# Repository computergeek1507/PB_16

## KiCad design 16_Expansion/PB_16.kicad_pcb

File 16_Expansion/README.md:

# Copyright and Disclaimer
Copyright: Scott Hanson

This documentation describes Open Hardware and is licensed under the CERN Open Hardware License Version 2 - Strongly Reciprocal. (CERN-OHL-S)

You may redistribute and modify this documentation under the terms of the CERN OHL-S-v2 (https://ohwr.org/cern_ohl_s_v2.txt). This documentation is distributed WITHOUT ANY EXPRESS OR IMPLIED WARRANTY, INCLUDING OF MERCHANTABILITY, SATISFACTORY QUALITY AND FITNESS FOR A PARTICULAR PURPOSE. Please see the CERN OHL v2-S for applicable conditions

**Under CERN OHL-S-v2, derivative work must be publicly released as defined in subsection 3.3**

# 16 Expansion

The "16 Expansion" is a 16 port output board for the PB16.  All the design files are open source and available on github.

## [Part BOM](https://github.com/computergeek1507/PB_16/raw/master/16_Expansion/16_Expansion_BOM.ods)

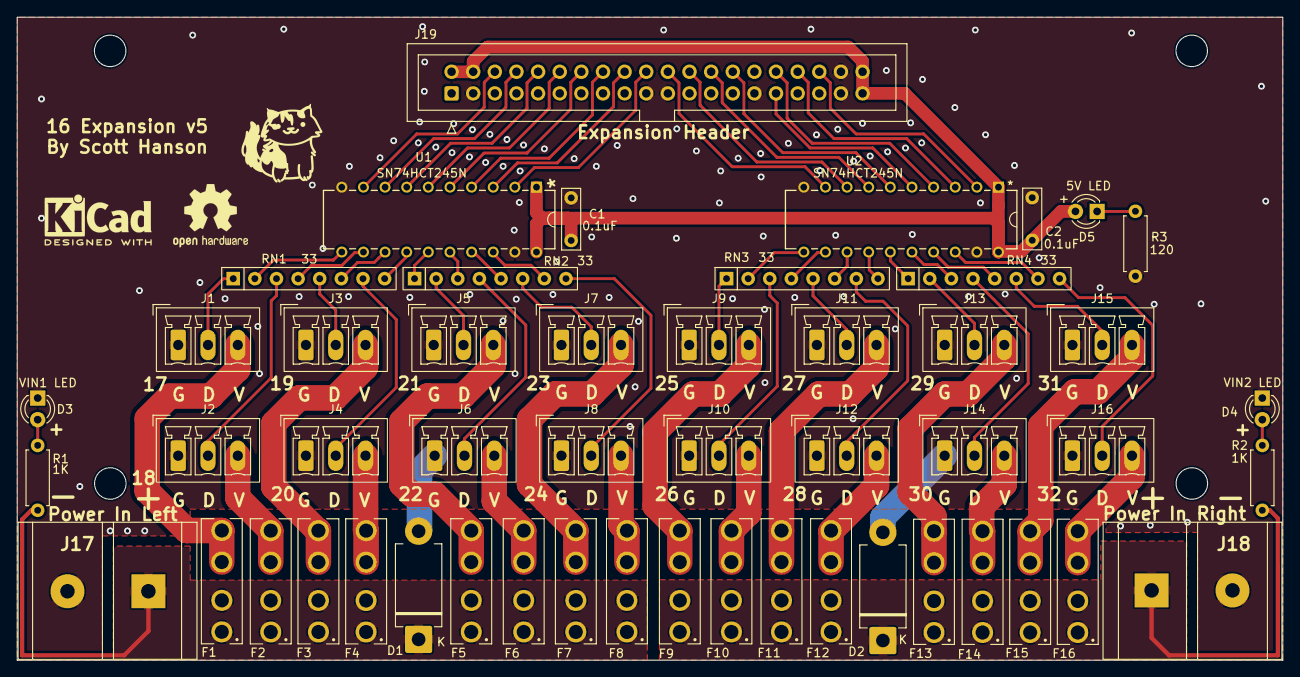
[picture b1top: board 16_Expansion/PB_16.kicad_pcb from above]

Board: 2 copper layers, 148.6 x 75.5 mm, 51 parts (0 on the bottom side), 71 nets.

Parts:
C1, C2: 0.1uF; C_Rect_L7.0mm_W2.0mm_P5.00mm
D1, D2: SB5100-T; D_DO-201AD_P12.70mm_Horizontal
D3: VIN1 LED; LED_D3.0mm
D4: VIN2 LED; LED_D3.0mm
D5: 5V LED; LED_D3.0mm
F1, F2, F3, F4, F5, F6, F7, F8, F9, F10, F11, F12, F13, F14, F15, F16: 3544-2; FUSE_3544-2
J1: String1; PhoenixContact_MCV_1,5_3-G-3.5_1x03_P3.50mm_Vertical
J2: String2; PhoenixContact_MCV_1,5_3-G-3.5_1x03_P3.50mm_Vertical
J3: String3; PhoenixContact_MCV_1,5_3-G-3.5_1x03_P3.50mm_Vertical
J4: String4; PhoenixContact_MCV_1,5_3-G-3.5_1x03_P3.50mm_Vertical
J5: String5; PhoenixContact_MCV_1,5_3-G-3.5_1x03_P3.50mm_Vertical
J6: String6; PhoenixContact_MCV_1,5_3-G-3.5_1x03_P3.50mm_Vertical
J7: String7; PhoenixContact_MCV_1,5_3-G-3.5_1x03_P3.50mm_Vertical
J8: String8; PhoenixContact_MCV_1,5_3-G-3.5_1x03_P3.50mm_Vertical
J9: String9; PhoenixContact_MCV_1,5_3-G-3.5_1x03_P3.50mm_Vertical
J10: String10; PhoenixContact_MCV_1,5_3-G-3.5_1x03_P3.50mm_Vertical
J11: String11; PhoenixContact_MCV_1,5_3-G-3.5_1x03_P3.50mm_Vertical
J12: String12; PhoenixContact_MCV_1,5_3-G-3.5_1x03_P3.50mm_Vertical
J13: String13; PhoenixContact_MCV_1,5_3-G-3.5_1x03_P3.50mm_Vertical
J14: String14; PhoenixContact_MCV_1,5_3-G-3.5_1x03_P3.50mm_Vertical
J15: String15; PhoenixContact_MCV_1,5_3-G-3.5_1x03_P3.50mm_Vertical
J16: String16; PhoenixContact_MCV_1,5_3-G-3.5_1x03_P3.50mm_Vertical
J17: Power In Left; BARRIER_BLOCK_1ROW_2POS_P9.5MM
J18: Power In Right; BARRIER_BLOCK_1ROW_2POS_P9.5MM
J19: Expansion Header; IDC-Header_2x20_P2.54mm_Vertical
R1, R2: 1K; R_Axial_DIN0207_L6.3mm_D2.5mm_P7.62mm_Horizontal
R3: 120; R_Axial_DIN0207_L6.3mm_D2.5mm_P7.62mm_Horizontal
RN1, RN2, RN3, RN4: 33; R_Array_SIP8
U1, U2: SN74HCT245N

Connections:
+5V: C1.1, C2.1, D5.2 (A), J19.2, J19.4, J19.39, J19.40, U1.1 (DIR), U1.20 (VCC), U2.1 (DIR), U2.20 (VCC)
/Output 1-8/DOUT1: J1.2, RN1.1 (R1.1)
/Output 1-8/DOUT2: J2.2, RN1.3 (R2.1)
/Output 1-8/DOUT3: J3.2, RN1.5 (R3.1)
/Output 1-8/DOUT4: J4.2, RN1.7 (R4.1)
/Output 1-8/DOUT5: J5.2, RN2.2 (R1.2)
/Output 1-8/DOUT6: J6.2, RN2.4 (R2.2)
/Output 1-8/DOUT7: J7.2, RN2.6 (R3.2)
/Output 1-8/DOUT8: J8.2, RN2.8 (R4.2)
/Output 1-8/VOUT1: F1.2_1 (2), F1.2_2 (2), J1.3
/Output 1-8/VOUT2: F2.2_1 (2), F2.2_2 (2), J2.3
/Output 1-8/VOUT3: F3.2_1 (2), F3.2_2 (2), J3.3
/Output 1-8/VOUT4: F4.2_1 (2), F4.2_2 (2), J4.3
/Output 1-8/VOUT5: F5.2_1 (2), F5.2_2 (2), J5.3
/Output 1-8/VOUT6: F6.2_1 (2), F6.2_2 (2), J6.3
/Output 1-8/VOUT7: F7.2_1 (2), F7.2_2 (2), J7.3
/Output 1-8/VOUT8: F8.2_1 (2), F8.2_2 (2), J8.3
/Output 9-16/DOUT9: J9.2, RN3.1 (R1.1)
/Output 9-16/DOUT10: J10.2, RN3.3 (R2.1)
/Output 9-16/DOUT11: J11.2, RN3.5 (R3.1)
/Output 9-16/DOUT12: J12.2, RN3.7 (R4.1)
/Output 9-16/DOUT13: J13.2, RN4.2 (R1.2)
/Output 9-16/DOUT14: J14.2, RN4.4 (R2.2)
/Output 9-16/DOUT15: J15.2, RN4.6 (R3.2)
/Output 9-16/DOUT16: J16.2, RN4.8 (R4.2)
/Output 9-16/VOUT9: F9.2_1 (2), F9.2_2 (2), J9.3
/Output 9-16/VOUT10: F10.2_1 (2), F10.2_2 (2), J10.3
/Output 9-16/VOUT11: F11.2_1 (2), F11.2_2 (2), J11.3
/Output 9-16/VOUT12: F12.2_1 (2), F12.2_2 (2), J12.3
/Output 9-16/VOUT13: F13.2_1 (2), F13.2_2 (2), J13.3
/Output 9-16/VOUT14: F14.2_1 (2), F14.2_2 (2), J14.3
/Output 9-16/VOUT15: F15.2_1 (2), F15.2_2 (2), J15.3
/Output 9-16/VOUT16: F16.2_1 (2), F16.2_2 (2), J16.3
GND: C1.2, C2.2, D1.2 (A), D2.2 (A), D3.1 (K), D4.1 (K), J1.1, J2.1, J3.1, J4.1, J5.1, J6.1, J7.1, J8.1, J9.1, J10.1, J11.1, J12.1, J13.1, J14.1, J15.1, J16.1, J17.2, J18.2, J19.3, J19.5, J19.7, J19.9, J19.11, J19.13, J19.15, J19.17, J19.19, J19.21, J19.23, J19.25, J19.27, J19.29, J19.33, J19.35, J19.37, J19.38, R3.1, U1.10 (GND), U1.19 (*OE), U2.10 (GND), U2.19 (*OE)
unnamed: D3.2 (A), R1.1
unnamed: D4.2 (A), R2.1
unnamed: D5.1 (K), R3.2
unnamed: RN1.2 (R1.2), U1.11 (B8)
unnamed: RN1.4 (R2.2), U1.12 (B7)
unnamed: RN1.6 (R3.2), U1.13 (B6)
unnamed: RN1.8 (R4.2), U1.14 (B5)
unnamed: RN2.1 (R1.1), U1.15 (B4)
unnamed: RN2.3 (R2.1), U1.16 (B3)
unnamed: RN2.5 (R3.1), U1.17 (B2)
unnamed: RN2.7 (R4.1), U1.18 (B1)
unnamed: RN3.2 (R1.2), U2.11 (B8)
unnamed: RN3.4 (R2.2), U2.12 (B7)
unnamed: RN3.6 (R3.2), U2.13 (B6)
unnamed: RN3.8 (R4.2), U2.14 (B5)
unnamed: RN4.1 (R1.1), U2.15 (B4)
unnamed: RN4.3 (R2.1), U2.16 (B3)
unnamed: RN4.5 (R3.1), U2.17 (B2)
unnamed: RN4.7 (R4.1), U2.18 (B1)
OUT17: J19.6, U1.9 (A8)
OUT18: J19.8, U1.8 (A7)
OUT19: J19.10, U1.7 (A6)
OUT20: J19.12, U1.6 (A5)
OUT21: J19.14, U1.5 (A4)
OUT22: J19.16, U1.4 (A3)
OUT23: J19.18, U1.3 (A2)
OUT24: J19.20, U1.2 (A1)
OUT25: J19.22, U2.9 (A8)
OUT26: J19.24, U2.8 (A7)
OUT27: J19.26, U2.7 (A6)
OUT28: J19.28, U2.6 (A5)
OUT29: J19.31, U2.5 (A4)
OUT30: J19.32, U2.4 (A3)
OUT31: J19.34, U2.3 (A2)
OUT32: J19.36, U2.2 (A1)
VIN1: D1.1 (K), F1.1_1 (1), F1.1_2 (1), F2.1_1 (1), F2.1_2 (1), F3.1_1 (1), F3.1_2 (1), F4.1_1 (1), F4.1_2 (1), F5.1_1 (1), F5.1_2 (1), F6.1_1 (1), F6.1_2 (1), F7.1_1 (1), F7.1_2 (1), F8.1_1 (1), F8.1_2 (1), J17.1, R1.2
VIN2: D2.1 (K), F9.1_1 (1), F9.1_2 (1), F10.1_1 (1), F10.1_2 (1), F11.1_1 (1), F11.1_2 (1), F12.1_1 (1), F12.1_2 (1), F13.1_1 (1), F13.1_2 (1), F14.1_1 (1), F14.1_2 (1), F15.1_1 (1), F15.1_2 (1), F16.1_1 (1), F16.1_2 (1), J18.1, R2.2

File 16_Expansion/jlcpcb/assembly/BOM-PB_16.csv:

Comment,Designator,Footprint,LCSC
0.1uF,C2,C_Rect_L7.0mm_W2.0mm_P5.00mm,
String2,J2,"PhoenixContact_MCV_1,5_3-G-3.5_1x03_P3.50mm_Vertical",
String5,J5,"PhoenixContact_MCV_1,5_3-G-3.5_1x03_P3.50mm_Vertical",
String6,J6,"PhoenixContact_MCV_1,5_3-G-3.5_1x03_P3.50mm_Vertical",
String7,J7,"PhoenixContact_MCV_1,5_3-G-3.5_1x03_P3.50mm_Vertical",
String8,J8,"PhoenixContact_MCV_1,5_3-G-3.5_1x03_P3.50mm_Vertical",
String9,J9,"PhoenixContact_MCV_1,5_3-G-3.5_1x03_P3.50mm_Vertical",
String10,J10,"PhoenixContact_MCV_1,5_3-G-3.5_1x03_P3.50mm_Vertical",
String11,J11,"PhoenixContact_MCV_1,5_3-G-3.5_1x03_P3.50mm_Vertical",
String12,J12,"PhoenixContact_MCV_1,5_3-G-3.5_1x03_P3.50mm_Vertical",
String13,J13,"PhoenixContact_MCV_1,5_3-G-3.5_1x03_P3.50mm_Vertical",
String14,J14,"PhoenixContact_MCV_1,5_3-G-3.5_1x03_P3.50mm_Vertical",
String15,J15,"PhoenixContact_MCV_1,5_3-G-3.5_1x03_P3.50mm_Vertical",
String16,J16,"PhoenixContact_MCV_1,5_3-G-3.5_1x03_P3.50mm_Vertical",
SN74HCT245N,U2,SN74HCT245N,
3544-2,F1,FUSE_3544-2,
3544-2,F7,FUSE_3544-2,
3544-2,F14,FUSE_3544-2,
SB5100-T,D2,D_DO-201AD_P12.70mm_Horizontal,
0.1uF,C1,C_Rect_L7.0mm_W2.0mm_P5.00mm,
3544-2,F2,FUSE_3544-2,
3544-2,F6,FUSE_3544-2,
3544-2,F8,FUSE_3544-2,
3544-2,F9,FUSE_3544-2,
3544-2,F10,FUSE_3544-2,
3544-2,F16,FUSE_3544-2,
3544-2,F5,FUSE_3544-2,
3544-2,F3,FUSE_3544-2,
3544-2,F13,FUSE_3544-2,
33,RN1,R_Array_SIP8,
3544-2,F11,FUSE_3544-2,
33,RN3,R_Array_SIP8,
33,RN4,R_Array_SIP8,
33,RN2,R_Array_SIP8,
3544-2,F4,FUSE_3544-2,
String1,J1,"PhoenixContact_MCV_1,5_3-G-3.5_1x03_P3.50mm_Vertical",
String3,J3,"PhoenixContact_MCV_1,5_3-G-3.5_1x03_P3.50mm_Vertical",
String4,J4,"PhoenixContact_MCV_1,5_3-G-3.5_1x03_P3.50mm_Vertical",
SB5100-T,D1,D_DO-201AD_P12.70mm_Horizontal,
3544-2,F15,FUSE_3544-2,
3544-2,F12,FUSE_3544-2,
SN74HCT245N,U1,SN74HCT245N,
VIN1 LED,D3,LED_D3.0mm_Clear,
1K,R1,R_Axial_DIN0207_L6.3mm_D2.5mm_P7.62mm_Horizontal,
5V LED,D5,LED_D3.0mm_Clear,
Expansion Header,J19,IDC-Header_2x20_P2.54mm_Vertical,
120,R3,R_Axial_DIN0207_L6.3mm_D2.5mm_P7.62mm_Horizontal,
Power In Left,J17,BARRIER_BLOCK_1ROW_2POS_P9.5MM,
Power In Right,J18,BARRIER_BLOCK_1ROW_2POS_P9.5MM,
1K,R2,R_Axial_DIN0207_L6.3mm_D2.5mm_P7.62mm_Horizontal,
VIN2 LED,D4,LED_D3.0mm_Clear,

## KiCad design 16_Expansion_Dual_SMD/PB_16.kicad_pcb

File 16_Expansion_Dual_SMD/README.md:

# Copyright and Disclaimer
Copyright: Scott Hanson

This documentation describes Open Hardware and is licensed under the CERN Open Hardware License Version 2 - Strongly Reciprocal. (CERN-OHL-S)

You may redistribute and modify this documentation under the terms of the CERN OHL-S-v2 (https://ohwr.org/cern_ohl_s_v2.txt). This documentation is distributed WITHOUT ANY EXPRESS OR IMPLIED WARRANTY, INCLUDING OF MERCHANTABILITY, SATISFACTORY QUALITY AND FITNESS FOR A PARTICULAR PURPOSE. Please see the CERN OHL v2-S for applicable conditions

**Under CERN OHL-S-v2, derivative work must be publicly released as defined in subsection 3.3**

# 16 Expansion Dual SMD

The "16 Expansion Dual SMD" is a 16 port output board for the PB16/BBB16. All the design files are open source and available on github.

To order PCBs upload the "GERBER-PB_16.zip" file in the "jlcpcb\gerber" folder to jlcpcb.com. Enable the SMD service, 'BOM-PB_16.csv' is the SMD BOM and 'POS-PB_16.csv' is the SMD CPL position file.

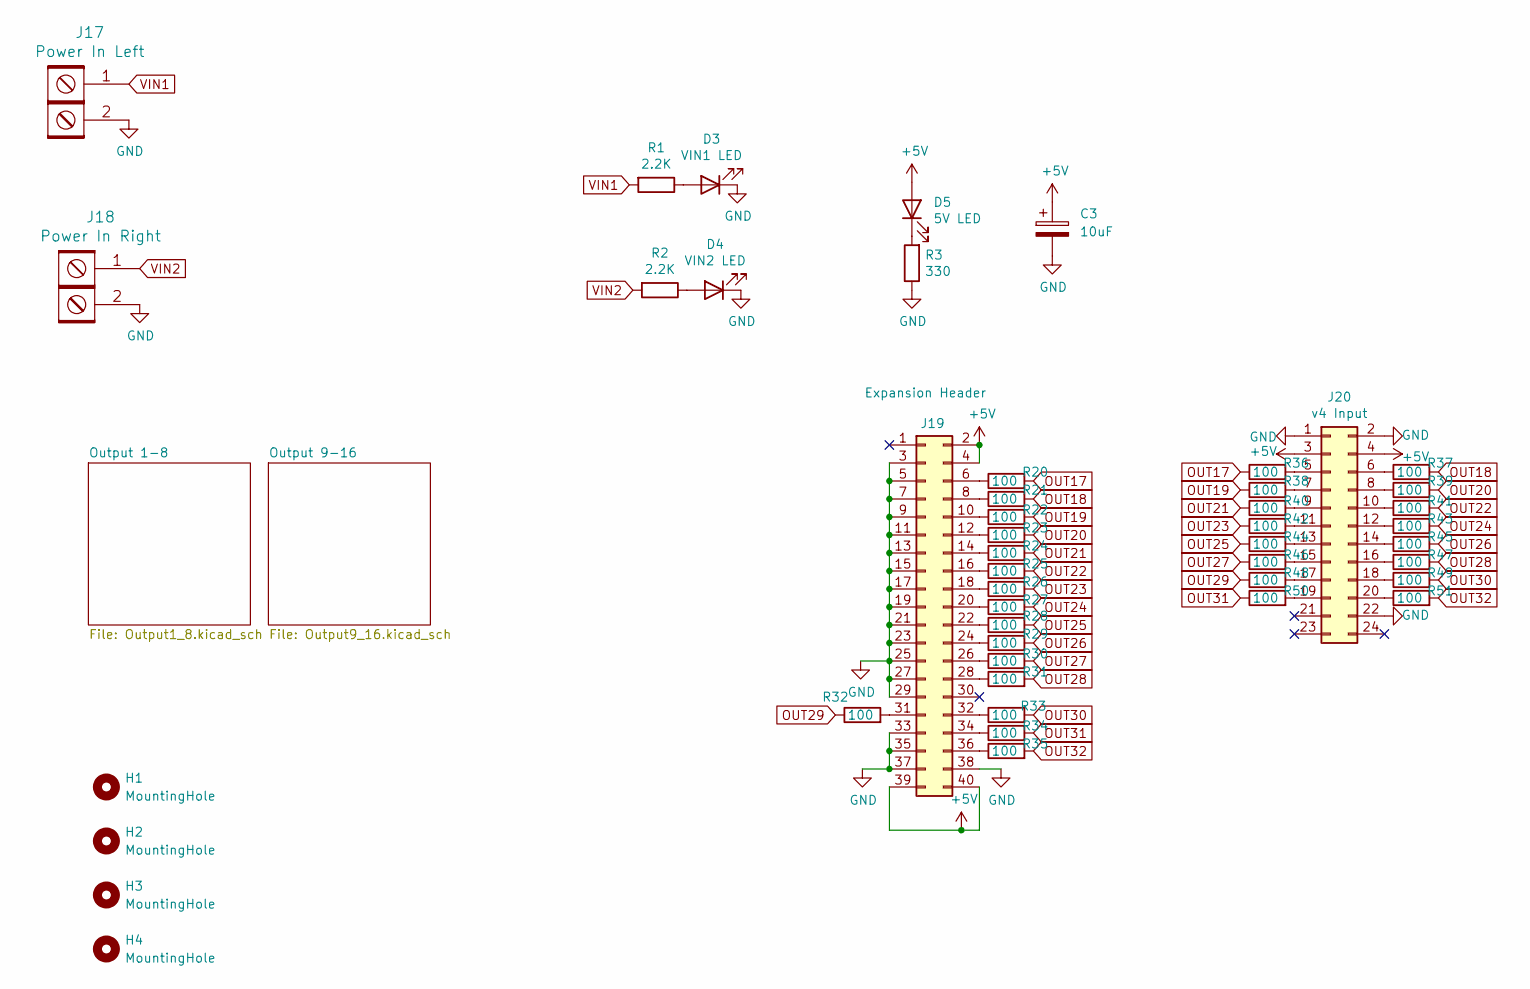
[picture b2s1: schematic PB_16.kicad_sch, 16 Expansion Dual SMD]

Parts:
C3: 10uF; CP_Elec_4x5.3; MPN UWT1C100MCL1GB; LCSC C72485
D3: VIN1 LED; LED_0603_1608Metric; MPN LTST-C190KRKT; Digi-Key_PN 160-1436-2-ND
D4: VIN2 LED; LED_0603_1608Metric; MPN LTST-C190KRKT; Digi-Key_PN 160-1436-2-ND
D5: 5V LED; LED_0603_1608Metric; MPN LTST-C190KRKT; Digi-Key_PN 160-1436-2-ND
H1, H2, H3, H4: MountingHole; MountingHole_3.7mm
J17: Power In Left; BARRIER_BLOCK_1ROW_2POS_P9.5MM; MPN OSTYK51102030; Digi-Key_PN ED2953-ND
J18: Power In Right; BARRIER_BLOCK_1ROW_2POS_P9.5MM; MPN OSTYK51102030; Digi-Key_PN ED2953-ND
J19: Expansion Header; IDC-Header_2x20_P2.54mm_Vertical; MPN SBH11-PBPC-D20-ST-BK; Digi-Key_PN S9175-ND
J20: v4 Input; OST_302-S241; MPN 302-S241; Digi-Key_PN ED10525-ND
R1: 2.2K; R_0603_1608Metric
R2: 2.2K; R_0603_1608Metric; MPN RC0603FR-071KL; Digi-Key_PN 311-1.00KHRTR-ND
R3: 330; R_0603_1608Metric; MPN RMCF0603JT330R; Digi-Key_PN RMCF0603JT330RCT-ND
R20, R21, R22, R23, R24, R25, R26, R27, R28, R29, R30, R31, R32, R33, R34, R35, R36, R37, R38, R39, R40, R41, R42, R43, R44, R45, R46, R47, R48, R49, R50, R51: 100; R_0603_1608Metric; MPN RMCF0603JT120R; Digi-Key_PN RMCF0603JT120RCT-ND

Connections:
+5V: C3.1, D5.2 (A), J19.2, J19.4, J19.39, J19.40, J20.3, J20.4; also elsewhere on the board
GND: C3.2, D3.1 (K), D4.1 (K), J17.2, J18.2, J19.3, J19.5, J19.7, J19.9, J19.11, J19.13, J19.15, J19.17, J19.19, J19.21, J19.23, J19.25, J19.27, J19.29, J19.33, J19.35, J19.37, J19.38, J20.1, J20.2, J20.22, R3.1; also elsewhere on the board
unnamed: D3.2 (A), R1.1
unnamed: D4.2 (A), R2.1
unnamed: D5.1 (K), R3.2
unnamed: J19.6, R20.1
unnamed: J19.8, R21.1
unnamed: J19.10, R22.1
unnamed: J19.12, R23.1
unnamed: J19.14, R24.1
unnamed: J19.16, R25.1
unnamed: J19.18, R26.1
unnamed: J19.20, R27.1
unnamed: J19.22, R28.1
unnamed: J19.24, R29.1
unnamed: J19.26, R30.1
unnamed: J19.28, R31.1
unnamed: J19.31, R32.2
unnamed: J19.32, R33.1
unnamed: J19.34, R34.1
unnamed: J19.36, R35.1
unnamed: J20.5, R36.2
unnamed: J20.6, R37.1
unnamed: J20.7, R38.2
unnamed: J20.8, R39.1
unnamed: J20.9, R40.2
unnamed: J20.10, R41.1
unnamed: J20.11, R42.2
unnamed: J20.12, R43.1
unnamed: J20.13, R44.2
unnamed: J20.14, R45.1
unnamed: J20.15, R46.2
unnamed: J20.16, R47.1
unnamed: J20.17, R48.2
unnamed: J20.18, R49.1
unnamed: J20.19, R50.2
unnamed: J20.20, R51.1
OUT17: R20.2, R36.1; also elsewhere on the board
OUT18: R21.2, R37.2; also elsewhere on the board
OUT19: R22.2, R38.1; also elsewhere on the board
OUT20: R23.2, R39.2; also elsewhere on the board
OUT21: R24.2, R40.1; also elsewhere on the board
OUT22: R25.2, R41.2; also elsewhere on the board
OUT23: R26.2, R42.1; also elsewhere on the board
OUT24: R27.2, R43.2; also elsewhere on the board
OUT25: R28.2, R44.1; also elsewhere on the board
OUT26: R29.2, R45.2; also elsewhere on the board
OUT27: R30.2, R46.1; also elsewhere on the board
OUT28: R31.2, R47.2; also elsewhere on the board
OUT29: R32.1, R48.1; also elsewhere on the board
OUT30: R33.2, R49.2; also elsewhere on the board
OUT31: R34.2, R50.1; also elsewhere on the board
OUT32: R35.2, R51.2; also elsewhere on the board
VIN1: J17.1, R1.2; also elsewhere on the board
VIN2: J18.1, R2.2; also elsewhere on the board

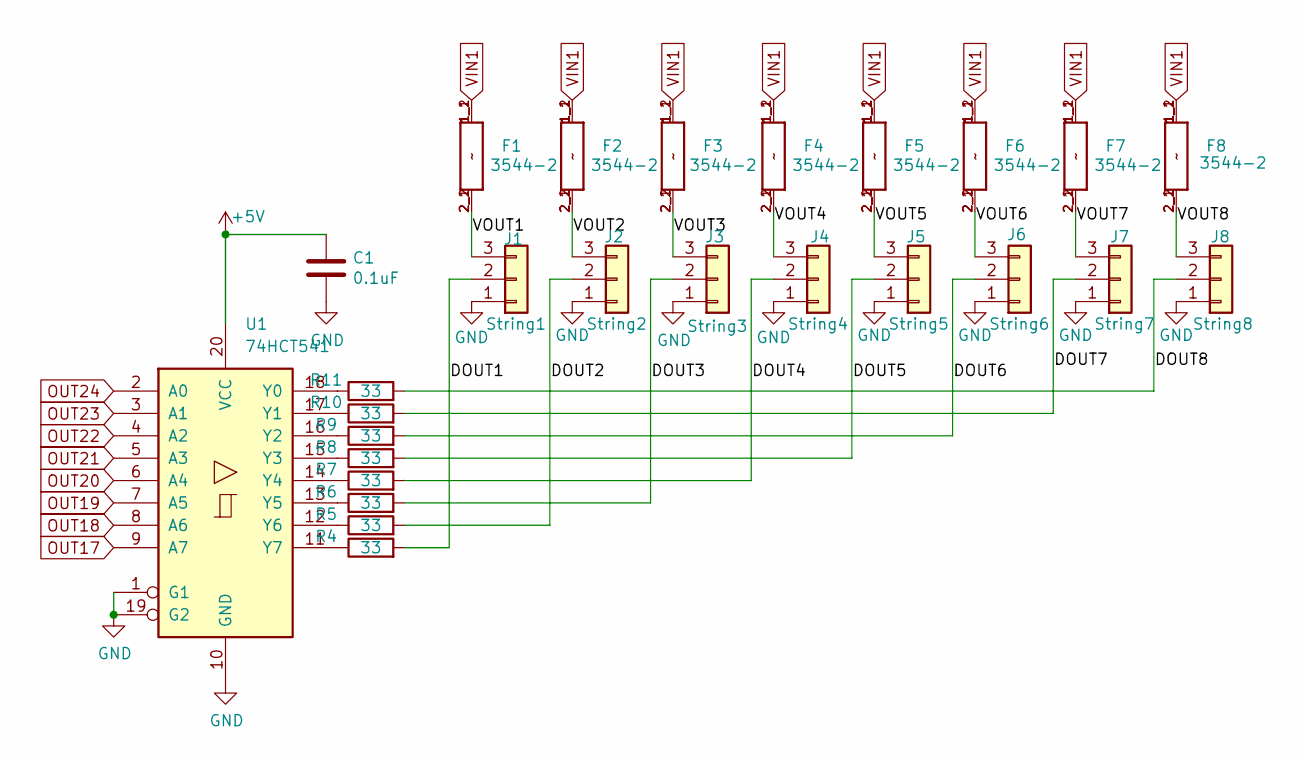
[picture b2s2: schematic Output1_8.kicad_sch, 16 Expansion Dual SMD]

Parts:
C1: 0.1uF; C_0402_1005Metric
F1, F2, F3, F4, F5, F6, F7, F8: 3544-2; FUSE_3544-2; MPN 3544-2; Digi-Key_PN 36-3544-2-ND
J1: String1; PhoenixContact_MCV_3.81mm_3.5mm_1x03_Vertical; MPN 1843619/OSTTJ0311530; Digi-Key_PN 277-5737-ND/ED10555-ND
J2: String2; PhoenixContact_MCV_3.81mm_3.5mm_1x03_Vertical; MPN 1843619/OSTTJ0311530; Digi-Key_PN 277-5737-ND/ED10555-ND
J3: String3; PhoenixContact_MCV_3.81mm_3.5mm_1x03_Vertical; MPN 1843619/OSTTJ0311530; Digi-Key_PN 277-5737-ND/ED10555-ND
J4: String4; PhoenixContact_MCV_3.81mm_3.5mm_1x03_Vertical; MPN 1843619/OSTTJ0311530; Digi-Key_PN 277-5737-ND/ED10555-ND
J5: String5; PhoenixContact_MCV_3.81mm_3.5mm_1x03_Vertical; MPN 1843619/OSTTJ0311530; Digi-Key_PN 277-5737-ND/ED10555-ND
J6: String6; PhoenixContact_MCV_3.81mm_3.5mm_1x03_Vertical; MPN 1843619/OSTTJ0311530; Digi-Key_PN 277-5737-ND/ED10555-ND
J7: String7; PhoenixContact_MCV_3.81mm_3.5mm_1x03_Vertical; MPN 1843619/OSTTJ0311530; Digi-Key_PN 277-5737-ND/ED10555-ND
J8: String8; PhoenixContact_MCV_3.81mm_3.5mm_1x03_Vertical; MPN 1843619/OSTTJ0311530; Digi-Key_PN 277-5737-ND/ED10555-ND
R4, R5, R6, R7, R8, R9, R10, R11: 33; R_0603_1608Metric; MPN CN34J330CT; LCSC C23140
U1: 74HCT541; TSSOP-20_4.4x6.5mm_P0.65mm

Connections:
+5V: C1.1, U1.20 (VCC); also elsewhere on the board
/Output 1-8/DOUT1: J1.2, R4.2
/Output 1-8/DOUT2: J2.2, R5.2
/Output 1-8/DOUT3: J3.2, R6.2
/Output 1-8/DOUT4: J4.2, R7.2
/Output 1-8/DOUT5: J5.2, R8.2
/Output 1-8/DOUT6: J6.2, R9.2
/Output 1-8/DOUT7: J7.2, R10.2
/Output 1-8/DOUT8: J8.2, R11.2
/Output 1-8/VOUT1: F1.2_1 (2), F1.2_2 (2), J1.3
/Output 1-8/VOUT2: F2.2_1 (2), F2.2_2 (2), J2.3
/Output 1-8/VOUT3: F3.2_1 (2), F3.2_2 (2), J3.3
/Output 1-8/VOUT4: F4.2_1 (2), F4.2_2 (2), J4.3
/Output 1-8/VOUT5: F5.2_1 (2), F5.2_2 (2), J5.3
/Output 1-8/VOUT6: F6.2_1 (2), F6.2_2 (2), J6.3
/Output 1-8/VOUT7: F7.2_1 (2), F7.2_2 (2), J7.3
/Output 1-8/VOUT8: F8.2_1 (2), F8.2_2 (2), J8.3
GND: C1.2, J1.1, J2.1, J3.1, J4.1, J5.1, J6.1, J7.1, J8.1, U1.1 (G1), U1.10 (GND), U1.19 (G2); also elsewhere on the board
unnamed: R11.1, U1.18 (Y0)
unnamed: R10.1, U1.17 (Y1)
unnamed: R9.1, U1.16 (Y2)
unnamed: R8.1, U1.15 (Y3)
unnamed: R7.1, U1.14 (Y4)
unnamed: R6.1, U1.13 (Y5)
unnamed: R5.1, U1.12 (Y6)
unnamed: R4.1, U1.11 (Y7)
OUT17: U1.9 (A7); also elsewhere on the board
OUT18: U1.8 (A6); also elsewhere on the board
OUT19: U1.7 (A5); also elsewhere on the board
OUT20: U1.6 (A4); also elsewhere on the board
OUT21: U1.5 (A3); also elsewhere on the board
OUT22: U1.4 (A2); also elsewhere on the board
OUT23: U1.3 (A1); also elsewhere on the board
OUT24: U1.2 (A0); also elsewhere on the board
VIN1: F1.1_1 (1), F1.1_2 (1), F2.1_1 (1), F2.1_2 (1), F3.1_1 (1), F3.1_2 (1), F4.1_1 (1), F4.1_2 (1), F5.1_1 (1), F5.1_2 (1), F6.1_1 (1), F6.1_2 (1), F7.1_1 (1), F7.1_2 (1), F8.1_1 (1), F8.1_2 (1); also elsewhere on the board

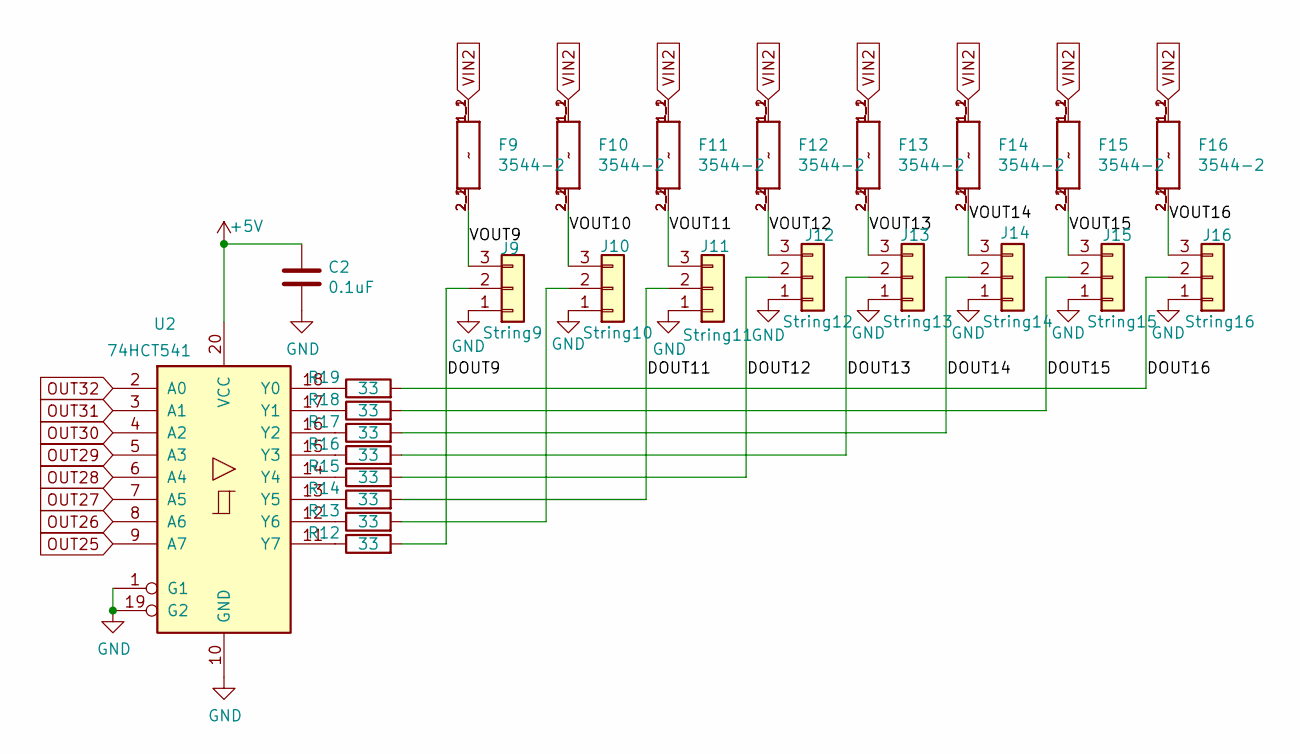
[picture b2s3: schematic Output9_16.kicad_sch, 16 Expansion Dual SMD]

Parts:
C2: 0.1uF; C_0402_1005Metric
F9, F10, F11, F12, F13, F14, F15, F16: 3544-2; FUSE_3544-2; MPN 3544-2; Digi-Key_PN 36-3544-2-ND
J9: String9; PhoenixContact_MCV_3.81mm_3.5mm_1x03_Vertical; MPN 1843619/OSTTJ0311530; Digi-Key_PN 277-5737-ND/ED10555-ND
J10: String10; PhoenixContact_MCV_3.81mm_3.5mm_1x03_Vertical; MPN 1843619/OSTTJ0311530; Digi-Key_PN 277-5737-ND/ED10555-ND
J11: String11; PhoenixContact_MCV_3.81mm_3.5mm_1x03_Vertical; MPN 1843619/OSTTJ0311530; Digi-Key_PN 277-5737-ND/ED10555-ND
J12: String12; PhoenixContact_MCV_3.81mm_3.5mm_1x03_Vertical; MPN 1843619/OSTTJ0311530; Digi-Key_PN 277-5737-ND/ED10555-ND
J13: String13; PhoenixContact_MCV_3.81mm_3.5mm_1x03_Vertical; MPN 1843619/OSTTJ0311530; Digi-Key_PN 277-5737-ND/ED10555-ND
J14: String14; PhoenixContact_MCV_3.81mm_3.5mm_1x03_Vertical; MPN 1843619/OSTTJ0311530; Digi-Key_PN 277-5737-ND/ED10555-ND
J15: String15; PhoenixContact_MCV_3.81mm_3.5mm_1x03_Vertical; MPN 1843619/OSTTJ0311530; Digi-Key_PN 277-5737-ND/ED10555-ND
J16: String16; PhoenixContact_MCV_3.81mm_3.5mm_1x03_Vertical; MPN 1843619/OSTTJ0311530; Digi-Key_PN 277-5737-ND/ED10555-ND
R12, R13, R14, R15, R16, R17, R18, R19: 33; R_0603_1608Metric; MPN CN34J330CT; LCSC C23140
U2: 74HCT541; TSSOP-20_4.4x6.5mm_P0.65mm

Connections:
+5V: C2.1, U2.20 (VCC); also elsewhere on the board
/Output 9-16/DOUT9: J9.2, R12.2
/Output 9-16/DOUT11: J11.2, R14.2
/Output 9-16/DOUT12: J12.2, R15.2
/Output 9-16/DOUT13: J13.2, R16.2
/Output 9-16/DOUT14: J14.2, R17.2
/Output 9-16/DOUT15: J15.2, R18.2
/Output 9-16/DOUT16: J16.2, R19.2
/Output 9-16/VOUT9: F9.2_1 (2), F9.2_2 (2), J9.3
/Output 9-16/VOUT10: F10.2_1 (2), F10.2_2 (2), J10.3
/Output 9-16/VOUT11: F11.2_1 (2), F11.2_2 (2), J11.3
/Output 9-16/VOUT12: F12.2_1 (2), F12.2_2 (2), J12.3
/Output 9-16/VOUT13: F13.2_1 (2), F13.2_2 (2), J13.3
/Output 9-16/VOUT14: F14.2_1 (2), F14.2_2 (2), J14.3
/Output 9-16/VOUT15: F15.2_1 (2), F15.2_2 (2), J15.3
/Output 9-16/VOUT16: F16.2_1 (2), F16.2_2 (2), J16.3
GND: C2.2, J9.1, J10.1, J11.1, J12.1, J13.1, J14.1, J15.1, J16.1, U2.1 (G1), U2.10 (GND), U2.19 (G2); also elsewhere on the board
unnamed: J10.2, R13.2
unnamed: R19.1, U2.18 (Y0)
unnamed: R18.1, U2.17 (Y1)
unnamed: R17.1, U2.16 (Y2)
unnamed: R16.1, U2.15 (Y3)
unnamed: R15.1, U2.14 (Y4)
unnamed: R14.1, U2.13 (Y5)
unnamed: R13.1, U2.12 (Y6)
unnamed: R12.1, U2.11 (Y7)
OUT25: U2.9 (A7); also elsewhere on the board
OUT26: U2.8 (A6); also elsewhere on the board
OUT27: U2.7 (A5); also elsewhere on the board
OUT28: U2.6 (A4); also elsewhere on the board
OUT29: U2.5 (A3); also elsewhere on the board
OUT30: U2.4 (A2); also elsewhere on the board
OUT31: U2.3 (A1); also elsewhere on the board
OUT32: U2.2 (A0); also elsewhere on the board
VIN2: F9.1_1 (1), F9.1_2 (1), F10.1_1 (1), F10.1_2 (1), F11.1_1 (1), F11.1_2 (1), F12.1_1 (1), F12.1_2 (1), F13.1_1 (1), F13.1_2 (1), F14.1_1 (1), F14.1_2 (1), F15.1_1 (1), F15.1_2 (1), F16.1_1 (1), F16.1_2 (1); also elsewhere on the board

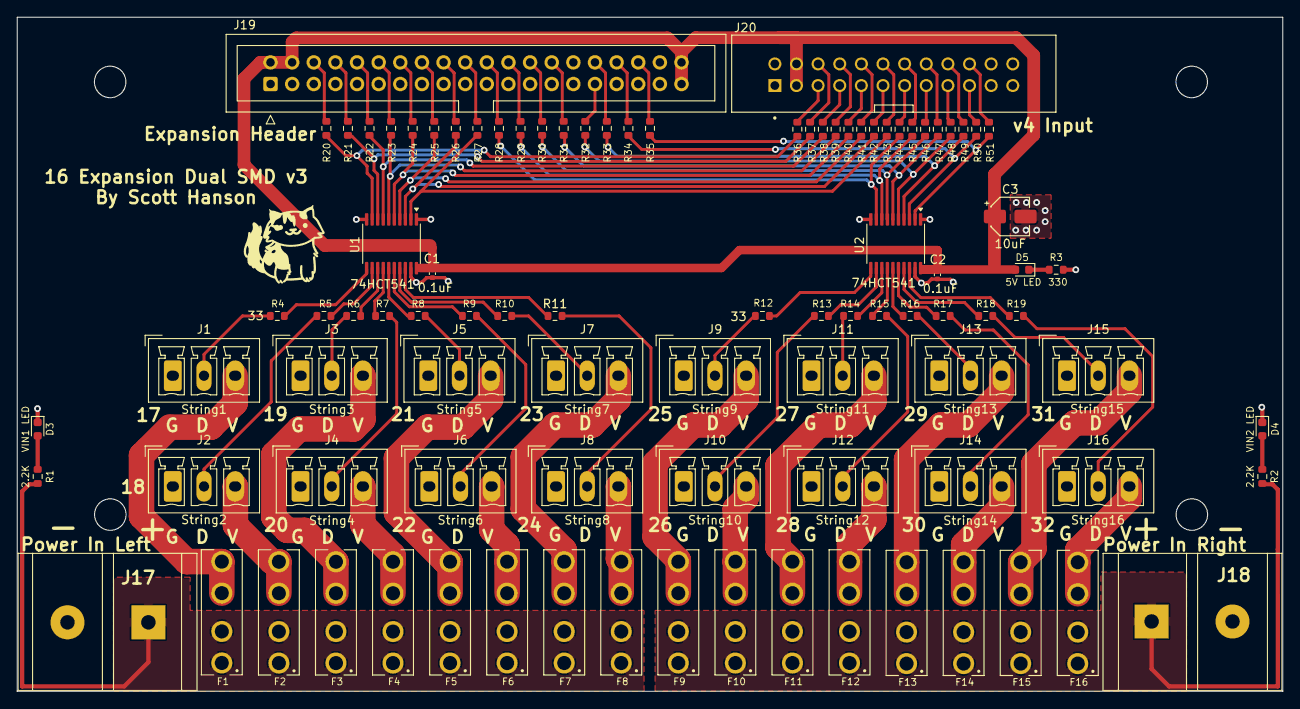
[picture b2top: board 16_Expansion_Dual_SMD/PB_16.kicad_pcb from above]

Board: 2 copper layers, 148.6 x 79.1 mm, 99 parts (0 on the bottom side), 103 nets.

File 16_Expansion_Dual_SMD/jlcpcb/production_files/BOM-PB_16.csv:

Comment,Designator,Footprint,LCSC,Quantity
0.1uF,"C1,C2",C_0402_1005Metric,C1525,2
100,"R20,R21,R22,R23,R24,R25,R26,R27,R28,R29,R30,R31,R32,R33,R34,R35,R36,R37,R38,R39,R40,R41,R42,R43,R44,R45,R46,R47,R48,R49,R50,R51",R_0603_1608Metric,C22775,32
10uF,C3,CP_Elec_4x5.3,C72485,1
2.2K,"R1,R2",R_0603_1608Metric,C4190,2
33,"R10,R11,R12,R13,R14,R15,R16,R17,R18,R19,R4,R5,R6,R7,R8,R9",R_0603_1608Metric,C23140,16
330,R3,R_0603_1608Metric,C23138,1
3544-2,"F1,F10,F11,F12,F13,F14,F15,F16,F2,F3,F4,F5,F6,F7,F8,F9",FUSE_3544-2,C492610,16
5V LED,D5,LED_0603_1608Metric,C2286,1
74HCT541,"U1,U2",TSSOP-20_4.4x6.5mm_P0.65mm,C436096,2
Expansion Header,J19,IDC-Header_2x20_P2.54mm_Vertical,C9138,1
Power In Left,J17,BARRIER_BLOCK_1ROW_2POS_P9.5MM,C707421,1
Power In Right,J18,BARRIER_BLOCK_1ROW_2POS_P9.5MM,C707421,1
String1,J1,PhoenixContact_MCV_3.81mm_3.5mm_1x03_Vertical,C192778,1
String10,J10,PhoenixContact_MCV_3.81mm_3.5mm_1x03_Vertical,C192778,1
String11,J11,PhoenixContact_MCV_3.81mm_3.5mm_1x03_Vertical,C192778,1
String12,J12,PhoenixContact_MCV_3.81mm_3.5mm_1x03_Vertical,C192778,1
String13,J13,PhoenixContact_MCV_3.81mm_3.5mm_1x03_Vertical,C192778,1
String14,J14,PhoenixContact_MCV_3.81mm_3.5mm_1x03_Vertical,C192778,1
String15,J15,PhoenixContact_MCV_3.81mm_3.5mm_1x03_Vertical,C192778,1
String16,J16,PhoenixContact_MCV_3.81mm_3.5mm_1x03_Vertical,C192778,1
String2,J2,PhoenixContact_MCV_3.81mm_3.5mm_1x03_Vertical,C192778,1
String3,J3,PhoenixContact_MCV_3.81mm_3.5mm_1x03_Vertical,C192778,1
String4,J4,PhoenixContact_MCV_3.81mm_3.5mm_1x03_Vertical,C192778,1
String5,J5,PhoenixContact_MCV_3.81mm_3.5mm_1x03_Vertical,C192778,1
String6,J6,PhoenixContact_MCV_3.81mm_3.5mm_1x03_Vertical,C192778,1
String7,J7,PhoenixContact_MCV_3.81mm_3.5mm_1x03_Vertical,C192778,1
String8,J8,PhoenixContact_MCV_3.81mm_3.5mm_1x03_Vertical,C192778,1
String9,J9,PhoenixContact_MCV_3.81mm_3.5mm_1x03_Vertical,C192778,1
VIN1 LED,D3,LED_0603_1608Metric,C2286,1
VIN2 LED,D4,LED_0603_1608Metric,C2286,1
v4 Input,J20,OST_302-S241,C221083,1

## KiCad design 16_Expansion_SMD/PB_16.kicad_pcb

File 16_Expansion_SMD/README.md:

# Copyright and Disclaimer
Copyright: Scott Hanson

This documentation describes Open Hardware and is licensed under the CERN Open Hardware License Version 2 - Strongly Reciprocal. (CERN-OHL-S)

You may redistribute and modify this documentation under the terms of the CERN OHL-S-v2 (https://ohwr.org/cern_ohl_s_v2.txt). This documentation is distributed WITHOUT ANY EXPRESS OR IMPLIED WARRANTY, INCLUDING OF MERCHANTABILITY, SATISFACTORY QUALITY AND FITNESS FOR A PARTICULAR PURPOSE. Please see the CERN OHL v2-S for applicable conditions

**Under CERN OHL-S-v2, derivative work must be publicly released as defined in subsection 3.3**

# 16 Expansion SMD

The "16 Expansion SMD" is a 16 port output board for the PB16.  All the design files are open source and available on github.

To order PCBs upload the "GERBER-PB_16.zip" file in the "jlcpcb\gerber" folder. Enable the SMD service, 'BOM-PB_16.csv' is the SMD BOM and 'POS-PB_16.csv' is the SMD CPL position file.

## [Part BOM](https://github.com/computergeek1507/PB_16/raw/master/16_Expansion_SMD/16_Expansion_BOM.ods)

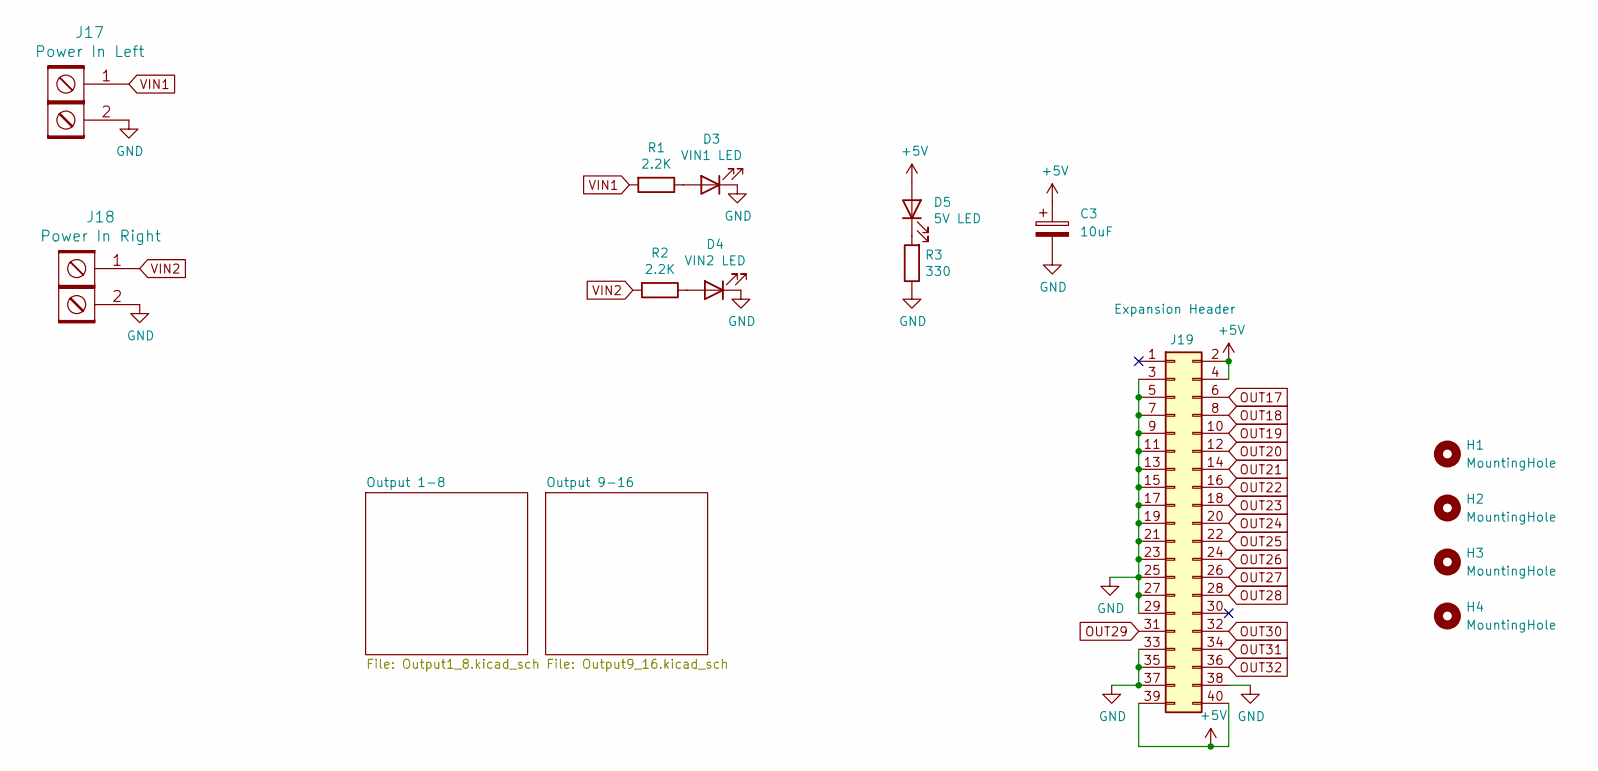
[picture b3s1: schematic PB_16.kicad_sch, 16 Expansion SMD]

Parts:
C3: 10uF; CP_Elec_4x5.3; MPN UWT1C100MCL1GB; LCSC C72485
D3: VIN1 LED; LED_0603_1608Metric; MPN 150080VS75000; Digi-Key_PN 732-4986-1-ND
D4: VIN2 LED; LED_0603_1608Metric; MPN 150080VS75000; Digi-Key_PN 732-4986-1-ND
D5: 5V LED; LED_0603_1608Metric; MPN 150080VS75000; Digi-Key_PN 732-4986-1-ND
H1, H2, H3, H4: MountingHole; MountingHole_3.7mm
J17: Power In Left; BARRIER_BLOCK_1ROW_2POS_P9.5MM; MPN OSTYK51102030; Digi-Key_PN ED2953-ND
J18: Power In Right; BARRIER_BLOCK_1ROW_2POS_P9.5MM; MPN OSTYK51102030; Digi-Key_PN ED2953-ND
J19: Expansion Header; IDC-Header_2x20_P2.54mm_Vertical; MPN SBH11-PBPC-D20-ST-BK; Digi-Key_PN S9175-ND
R1, R2: 2.2K; R_0603_1608Metric; MPN RC0805FR-071KL; Digi-Key_PN 311-1.00KCRCT-ND
R3: 330; R_0603_1608Metric; MPN RC0805FR-07330RL; Digi-Key_PN 311-330CRCT-ND

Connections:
+5V: C3.1, D5.2 (A), J19.2, J19.4, J19.39, J19.40; also elsewhere on the board
GND: C3.2, D3.1 (K), D4.1 (K), J17.2, J18.2, J19.3, J19.5, J19.7, J19.9, J19.11, J19.13, J19.15, J19.17, J19.19, J19.21, J19.23, J19.25, J19.27, J19.29, J19.33, J19.35, J19.37, J19.38, R3.1; also elsewhere on the board
unnamed: D3.2 (A), R1.1
unnamed: D4.2 (A), R2.1
unnamed: D5.1 (K), R3.2
OUT17: J19.6; also elsewhere on the board
OUT18: J19.8; also elsewhere on the board
OUT19: J19.10; also elsewhere on the board
OUT20: J19.12; also elsewhere on the board
OUT21: J19.14; also elsewhere on the board
OUT22: J19.16; also elsewhere on the board
OUT23: J19.18; also elsewhere on the board
OUT24: J19.20; also elsewhere on the board
OUT25: J19.22; also elsewhere on the board
OUT26: J19.24; also elsewhere on the board
OUT27: J19.26; also elsewhere on the board
OUT28: J19.28; also elsewhere on the board
OUT29: J19.31; also elsewhere on the board
OUT30: J19.32; also elsewhere on the board
OUT31: J19.34; also elsewhere on the board
OUT32: J19.36; also elsewhere on the board
VIN1: J17.1, R1.2; also elsewhere on the board
VIN2: J18.1, R2.2; also elsewhere on the board

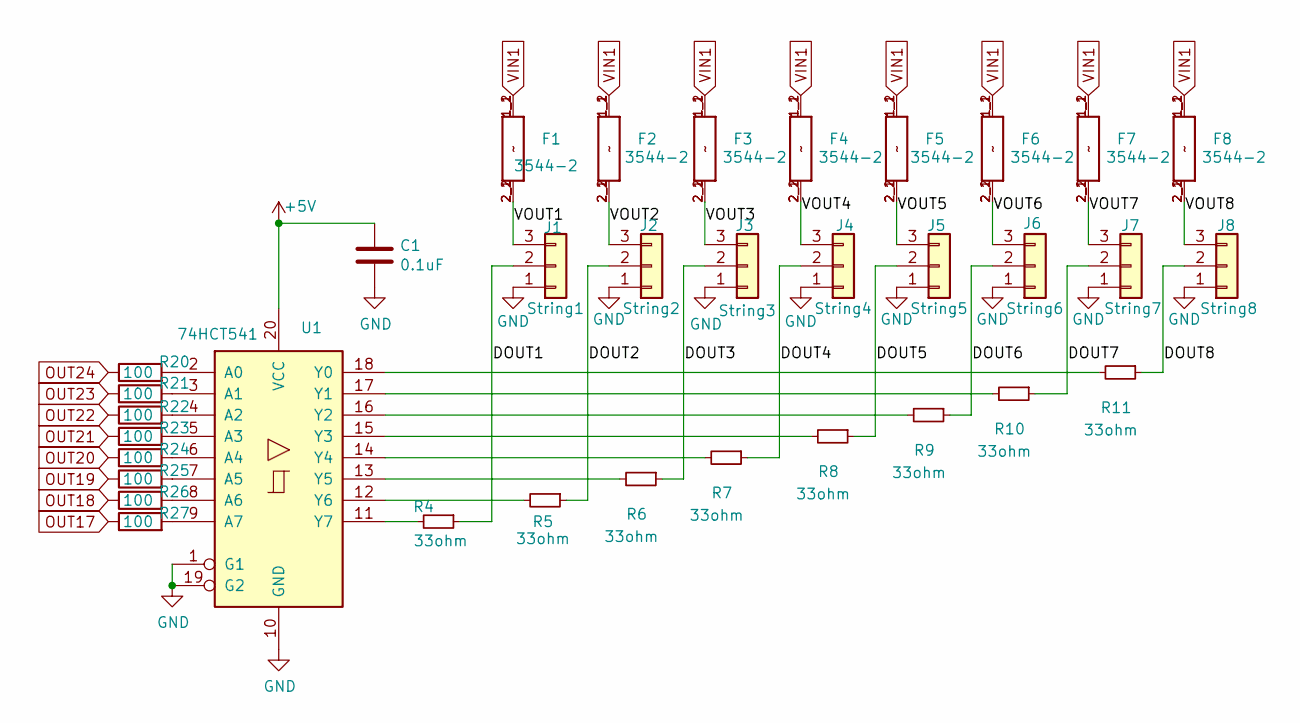
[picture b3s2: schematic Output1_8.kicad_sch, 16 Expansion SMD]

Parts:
C1: 0.1uF; C_0402_1005Metric; MPN 08055C104KAT2A; Digi-Key_PN 478-1395-1-ND
F1, F2, F3, F4, F5, F6, F7, F8: 3544-2; FUSE_3544-2; MPN 3544-2; Digi-Key_PN 36-3544-2-ND
J1: String1; PhoenixContact_MCV_3.81mm_3.5mm_1x03_Vertical; MPN 1843619/OSTTJ0311530; Digi-Key_PN 277-5737-ND/ED10555-ND
J2: String2; PhoenixContact_MCV_3.81mm_3.5mm_1x03_Vertical; MPN 1843619/OSTTJ0311530; Digi-Key_PN 277-5737-ND/ED10555-ND
J3: String3; PhoenixContact_MCV_3.81mm_3.5mm_1x03_Vertical; MPN 1843619/OSTTJ0311530; Digi-Key_PN 277-5737-ND/ED10555-ND
J4: String4; PhoenixContact_MCV_3.81mm_3.5mm_1x03_Vertical; MPN 1843619/OSTTJ0311530; Digi-Key_PN 277-5737-ND/ED10555-ND
J5: String5; PhoenixContact_MCV_3.81mm_3.5mm_1x03_Vertical; MPN 1843619/OSTTJ0311530; Digi-Key_PN 277-5737-ND/ED10555-ND
J6: String6; PhoenixContact_MCV_3.81mm_3.5mm_1x03_Vertical; MPN 1843619/OSTTJ0311530; Digi-Key_PN 277-5737-ND/ED10555-ND
J7: String7; PhoenixContact_MCV_3.81mm_3.5mm_1x03_Vertical; MPN 1843619/OSTTJ0311530; Digi-Key_PN 277-5737-ND/ED10555-ND
J8: String8; PhoenixContact_MCV_3.81mm_3.5mm_1x03_Vertical; MPN 1843619/OSTTJ0311530; Digi-Key_PN 277-5737-ND/ED10555-ND
R4, R5, R6, R7, R8, R9, R10, R11: 33ohm; R_0603_1608Metric; MPN RC0603JR-0733RL; LCSC_PN C23140
R20, R21, R22, R23, R24, R25, R26, R27: 100; R_0603_1608Metric
U1: 74HCT541; TSSOP-20_4.4x6.5mm_P0.65mm; LCSC C131314

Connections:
+5V: C1.1, U1.20 (VCC); also elsewhere on the board
/Output 1-8/DOUT1: J1.2, R4.1
/Output 1-8/DOUT2: J2.2, R5.1
/Output 1-8/DOUT3: J3.2, R6.1
/Output 1-8/DOUT4: J4.2, R7.1
/Output 1-8/DOUT5: J5.2, R8.1
/Output 1-8/DOUT6: J6.2, R9.1
/Output 1-8/DOUT7: J7.2, R10.1
/Output 1-8/DOUT8: J8.2, R11.1
/Output 1-8/VOUT1: F1.2_1 (2), F1.2_2 (2), J1.3
/Output 1-8/VOUT2: F2.2_1 (2), F2.2_2 (2), J2.3
/Output 1-8/VOUT3: F3.2_1 (2), F3.2_2 (2), J3.3
/Output 1-8/VOUT4: F4.2_1 (2), F4.2_2 (2), J4.3
/Output 1-8/VOUT5: F5.2_1 (2), F5.2_2 (2), J5.3
/Output 1-8/VOUT6: F6.2_1 (2), F6.2_2 (2), J6.3
/Output 1-8/VOUT7: F7.2_1 (2), F7.2_2 (2), J7.3
/Output 1-8/VOUT8: F8.2_1 (2), F8.2_2 (2), J8.3
GND: C1.2, J1.1, J2.1, J3.1, J4.1, J5.1, J6.1, J7.1, J8.1, U1.1 (G1), U1.10 (GND), U1.19 (G2); also elsewhere on the board
unnamed: R20.2, U1.2 (A0)
unnamed: R21.2, U1.3 (A1)
unnamed: R22.2, U1.4 (A2)
unnamed: R23.2, U1.5 (A3)
unnamed: R24.2, U1.6 (A4)
unnamed: R25.2, U1.7 (A5)
unnamed: R26.2, U1.8 (A6)
unnamed: R27.2, U1.9 (A7)
unnamed: R11.2, U1.18 (Y0)
unnamed: R10.2, U1.17 (Y1)
unnamed: R9.2, U1.16 (Y2)
unnamed: R8.2, U1.15 (Y3)
unnamed: R7.2, U1.14 (Y4)
unnamed: R6.2, U1.13 (Y5)
unnamed: R5.2, U1.12 (Y6)
unnamed: R4.2, U1.11 (Y7)
OUT17: R27.1; also elsewhere on the board
OUT18: R26.1; also elsewhere on the board
OUT19: R25.1; also elsewhere on the board
OUT20: R24.1; also elsewhere on the board
OUT21: R23.1; also elsewhere on the board
OUT22: R22.1; also elsewhere on the board
OUT23: R21.1; also elsewhere on the board
OUT24: R20.1; also elsewhere on the board
VIN1: F1.1_1 (1), F1.1_2 (1), F2.1_1 (1), F2.1_2 (1), F3.1_1 (1), F3.1_2 (1), F4.1_1 (1), F4.1_2 (1), F5.1_1 (1), F5.1_2 (1), F6.1_1 (1), F6.1_2 (1), F7.1_1 (1), F7.1_2 (1), F8.1_1 (1), F8.1_2 (1); also elsewhere on the board

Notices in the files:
parts and their libraries:
Copyright 2016 Accelerated Designs. All rights reserved.
